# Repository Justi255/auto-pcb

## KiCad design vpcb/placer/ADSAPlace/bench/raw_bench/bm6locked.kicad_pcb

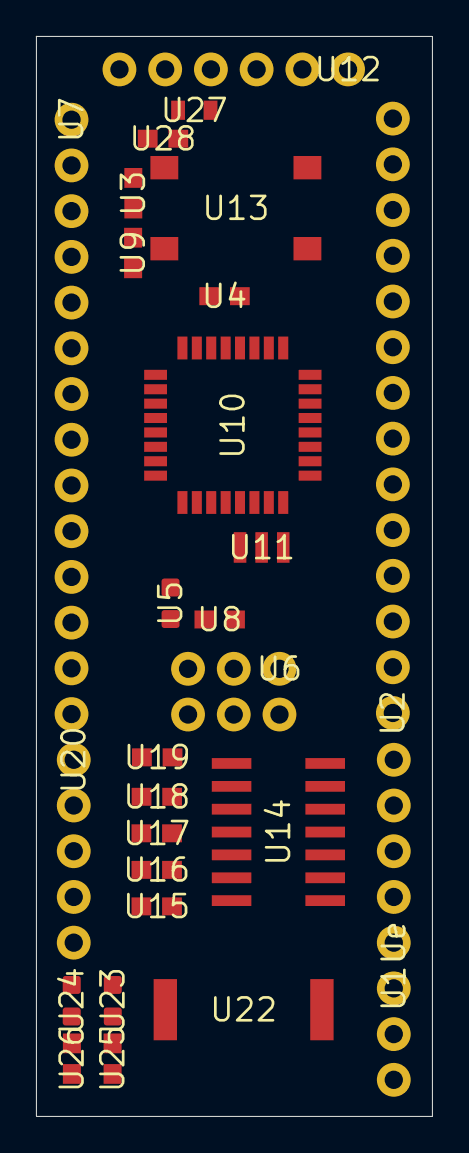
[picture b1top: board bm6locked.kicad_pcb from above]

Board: 2 copper layers, 22.0 x 60.0 mm, 28 parts (0 on the bottom side), 51 nets, no tracks yet.

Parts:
U1: 1X03
U2, U7: 1X14
U3, U4, U8, U9, U15, U16, U17, U18, U19, U25, U26, U28: 0603
U5, U23, U24: LED-0603
U6: 2X3
U10: TQFP32-08
U11: RESONATOR-SMD
U12: FTDI_BASIC
U13: TACTILE_SWITCH_SMD_6.2MM_TALL
U14: SO14
U20: 1X05
U22: PKMCS
U27: FUSC1608X100N
Ue: 1X05

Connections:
/A0: U7.7, U10.23
/A1: U7.8, U10.24
/A2: U7.9, U10.25
/A3: U7.10, U10.26
/A4: U7.11, U10.27
/A5: U7.12, U10.28
/A6: U7.13, U10.19
/A7: U7.14, U10.22
/D2: U2.3, U10.32
/D3: U2.4, U10.1
/D4: U2.5, U10.2
/D5: U2.6, U10.9
/D6: U2.7, U10.10
/D7: U2.8, U10.11
/D8: U2.9, U10.12
/D9: U2.10, U10.13
/D10: U2.11, U10.14
/DTR: U3.1, U12.DTR
/GO: U14.3, Ue.1
/MISO: U2.13, U6.1, U10.16
/MOSI: U2.12, U6.4, U10.15
/OUT1: U14.8, Ue.2
/OUT2: U14.7, Ue.3
/OUT3: U14.6, Ue.4
/OUT4: U14.5, Ue.5
/RST: U3.2, U6.5, U9.1, U10.29, U13.B2
/RXI: U7.5, U10.30, U12.TXO
/SCK: U2.14, U6.3, U8.1, U10.17
/TXO: U7.6, U10.31, U12.RXI
GND: U2.2, U4.2, U5.C, U6.6, U7.4, U10.3, U10.5, U10.21, U11.2, U12.GND, U13.A2, U14.14, U22.1, U23.C, U24.C, U28.2
unnamed: U4.1, U10.20
unnamed: U5.A, U8.2
unnamed: U23.A, U25.1
unnamed: U24.A, U26.1
unnamed: U12.VCC, U27.1
unnamed: U14.9, U19.2
unnamed: U14.10, U18.2
unnamed: U14.11, U17.2
unnamed: U14.12, U16.2
unnamed: U14.13, U15.2
unnamed: U19.1, U20.1
unnamed: U18.1, U20.2
unnamed: U17.1, U20.3
unnamed: U16.1, U20.4
unnamed: U15.1, U20.5
unnamed: U1.1, U22.2
unnamed: U1.2, U25.2
unnamed: U1.3, U26.2
unnamed: U10.7, U11.3
unnamed: U10.8, U11.1
VCC: U2.1, U6.2, U7.1, U7.2, U7.3, U9.2, U10.4, U10.6, U10.18, U14.1, U14.2, U14.4, U27.2, U28.1
